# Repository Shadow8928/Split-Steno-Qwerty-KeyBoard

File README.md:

# Split-Steno-Qwerty-Keyboard

Modular and split keyboard designed to be affordable and easy to solder. 

Usage: create the 4 different pcbs and their respective cases solder all the components then flash the software (More detailes to be added later)
Taking inspiration from 2 keyboards a single keyboard used for stenography and another keyboard used for both stenography and qwerty typing i designed a keyboard with a layout of the 2 somewhat combined also split down the middle with a wire to connect them together. now the keyboard should be able to type in stenography for which it should have n-key rollover as well as all the keys to type regular qwerty style.   

The only requirements are a computer with the port to connect the keyboard and plover setup and configured on that same computer.

| Part    | Quantity | Price |
| ------- | -------- |-------|
| Type C recepticle 5 pack  |  1 | $2.44|
| RaspBerry Pi Pico | 2     |$5.20|
| Pogo connector 5 pack    | 1    |$1.23|
|Diodes 100pc|1|$1.88|
|Mechanical switches 50pc|1|$9.55|
|Total keyboard|1|$20.30|

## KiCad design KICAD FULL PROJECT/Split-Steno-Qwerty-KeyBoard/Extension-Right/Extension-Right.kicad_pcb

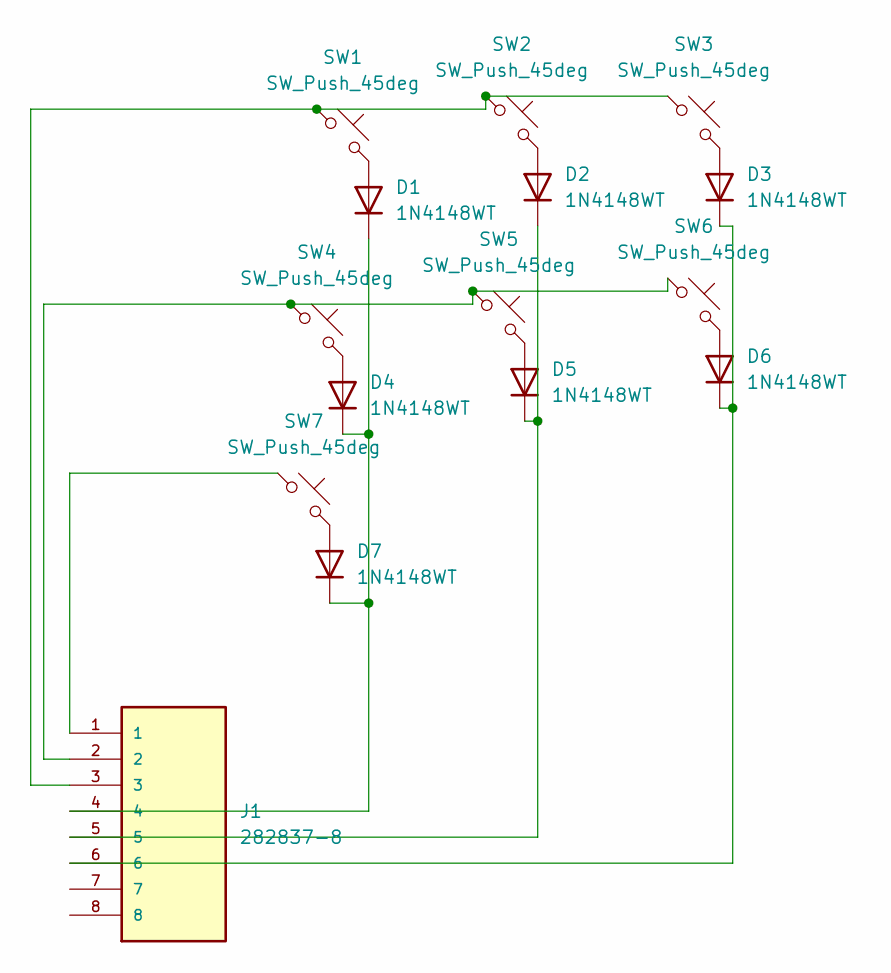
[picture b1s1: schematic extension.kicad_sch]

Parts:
D1, D2, D3, D4, D5, D6, D7: 1N4148WT; D_SOD-523
J1: 282837-8; TE_282837-8; PARTREV H
SW1, SW2, SW3, SW4, SW5, SW6, SW7: SW_Push_45deg; SW_Cherry_MX_1.00u_PCB

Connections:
unnamed: D1.2 (A), SW1.2
unnamed: D1.1 (K), D4.1 (K), D7.1 (K), J1.4
unnamed: D2.2 (A), SW2.2
unnamed: D2.1 (K), D5.1 (K), J1.5
unnamed: D3.2 (A), SW3.2
unnamed: D3.1 (K), D6.1 (K), J1.6
unnamed: D4.2 (A), SW4.2
unnamed: D5.2 (A), SW5.2
unnamed: D6.2 (A), SW6.2
unnamed: D7.2 (A), SW7.2
unnamed: J1.1, SW7.1
unnamed: J1.2, SW4.1, SW5.1, SW6.1
unnamed: J1.3, SW1.1, SW2.1, SW3.1

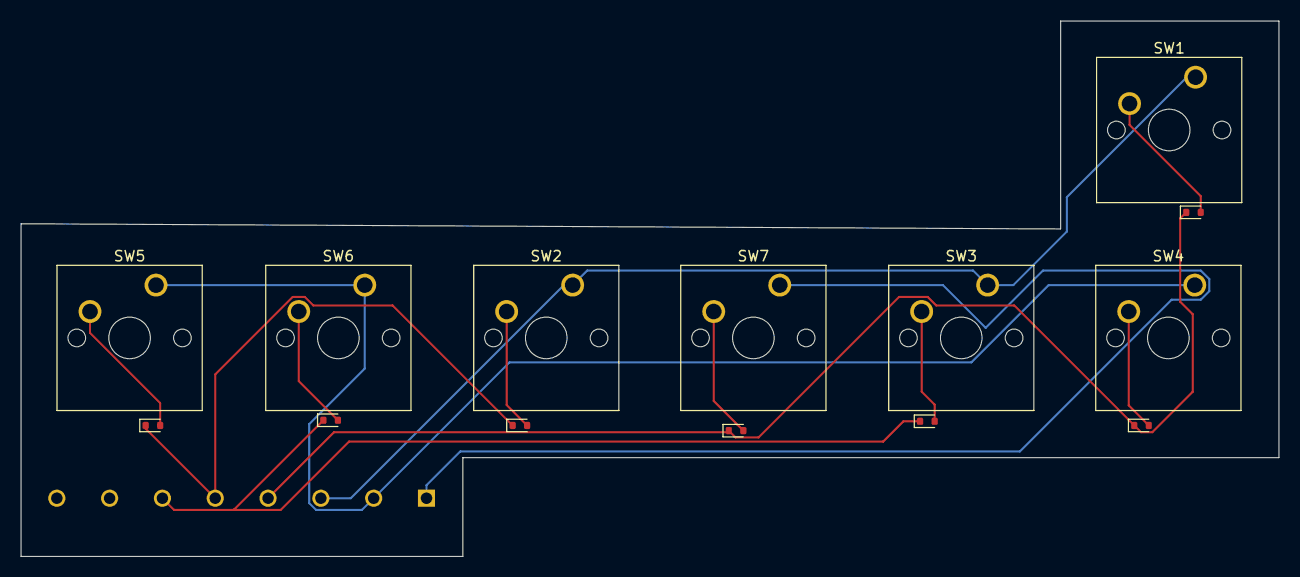
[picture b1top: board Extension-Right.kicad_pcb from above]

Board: 2 copper layers, 121.0 x 51.5 mm, 15 parts (1 on the bottom side), 13 nets.

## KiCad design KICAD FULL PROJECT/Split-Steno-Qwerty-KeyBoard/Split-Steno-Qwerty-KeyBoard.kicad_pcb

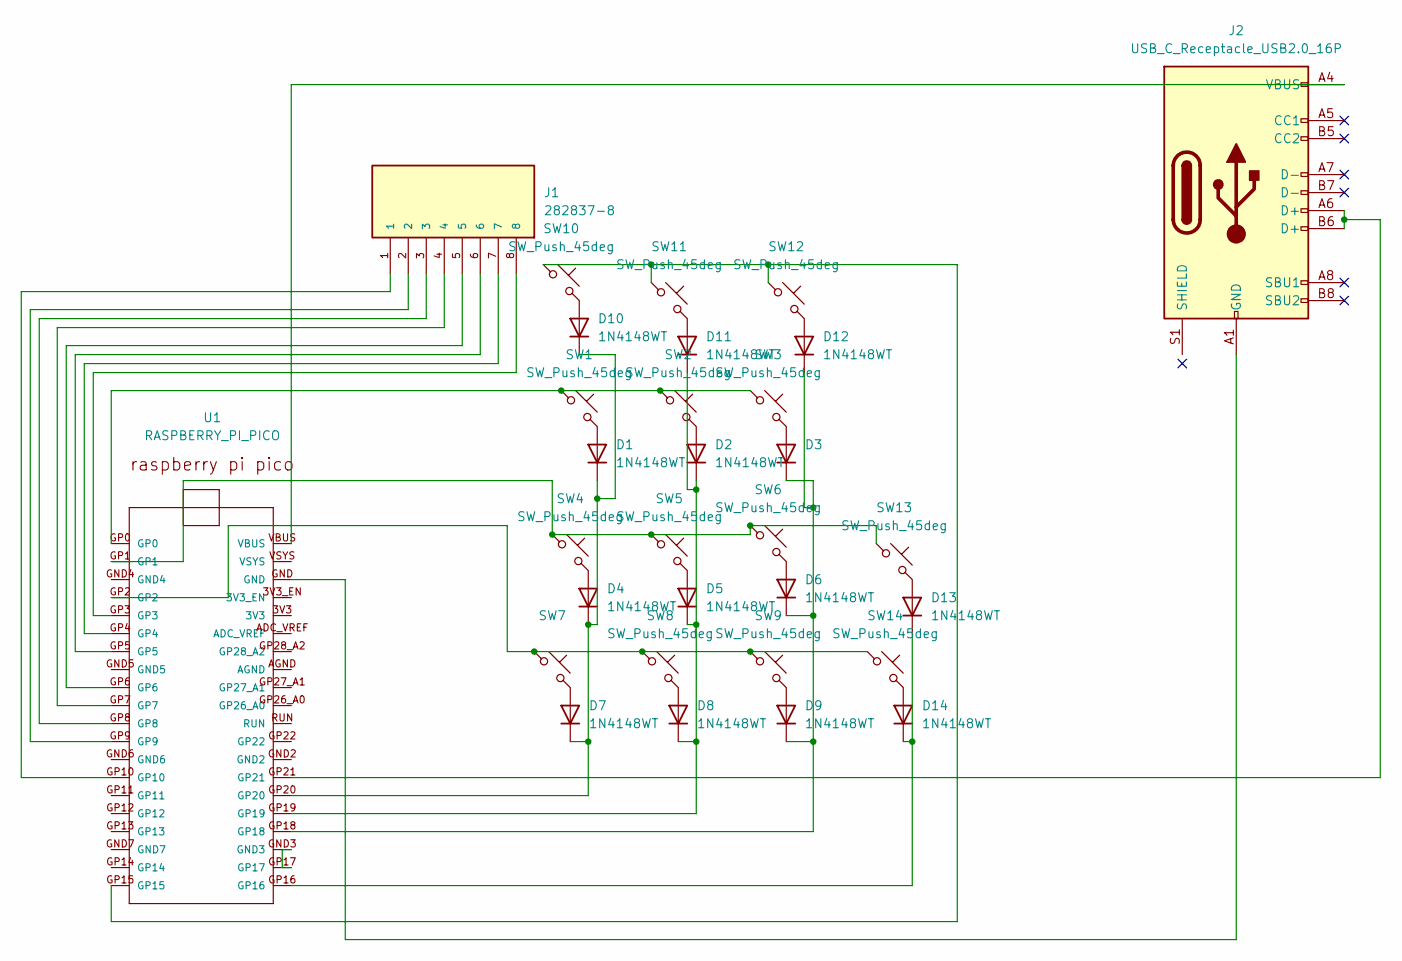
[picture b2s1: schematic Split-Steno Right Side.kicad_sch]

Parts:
D1, D2, D3, D4, D5, D6, D7, D8, D9, D10, D11, D12, D13, D14: 1N4148WT; D_SOD-523
J1: 282837-8; TE_282837-8; PARTREV H
J2: USB_C_Receptacle_USB2.0_16P; USB_C_Receptacle_XKB_U262-16XN-4BVC11
SW1, SW2, SW3, SW4, SW5, SW6, SW7, SW8, SW9, SW10, SW11, SW12, SW13, SW14: SW_Push_45deg; SW_MX_1u
U1: RASPBERRY_PI_PICO

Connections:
unnamed: D1.2 (A), SW1.2
unnamed: D1.1 (K), D4.1 (K), D7.1 (K), D10.1 (K), U1.GP20
unnamed: D2.2 (A), SW2.2
unnamed: D3.2 (A), SW3.2
unnamed: D4.2 (A), SW4.2
unnamed: D5.2 (A), SW5.2
unnamed: D6.2 (A), SW6.2
unnamed: D7.2 (A), SW7.2
unnamed: D8.2 (A), SW8.2
unnamed: D9.2 (A), SW9.2
unnamed: D10.2 (A), SW10.2
unnamed: D11.2 (A), SW11.2
unnamed: D2.1 (K), D5.1 (K), D8.1 (K), D11.1 (K), U1.GP19
unnamed: D12.2 (A), SW12.2
unnamed: D3.1 (K), D6.1 (K), D9.1 (K), D12.1 (K), U1.GP18
unnamed: D13.2 (A), SW13.2
unnamed: D13.1 (K), D14.1 (K), U1.GP16
unnamed: D14.2 (A), SW14.2
unnamed: J1.1, U1.GP10
unnamed: J1.2, U1.GP9
unnamed: J1.3, U1.GP8
unnamed: J1.4, U1.GP7
unnamed: J1.5, U1.GP6
unnamed: J1.6, U1.GP5
unnamed: J1.7, U1.GP4
unnamed: J1.8, U1.GP3
unnamed: J2.A6 (D+), J2.B6 (D+), U1.GP21
unnamed: J2.A1 (GND), J2.A12 (GND), J2.B1 (GND), J2.B12 (GND), U1.GND
unnamed: J2.A4 (VBUS), J2.A9 (VBUS), J2.B4 (VBUS), J2.B9 (VBUS), U1.VBUS
unnamed: SW1.1, SW2.1, SW3.1, U1.GP0
unnamed: SW10.1, SW11.1, SW12.1, U1.GP15
unnamed: SW4.1, SW5.1, SW6.1, SW13.1, U1.GP1
unnamed: SW7.1, SW8.1, SW9.1, SW14.1, U1.GP2
unnamed: U1.GND3, U1.GP17

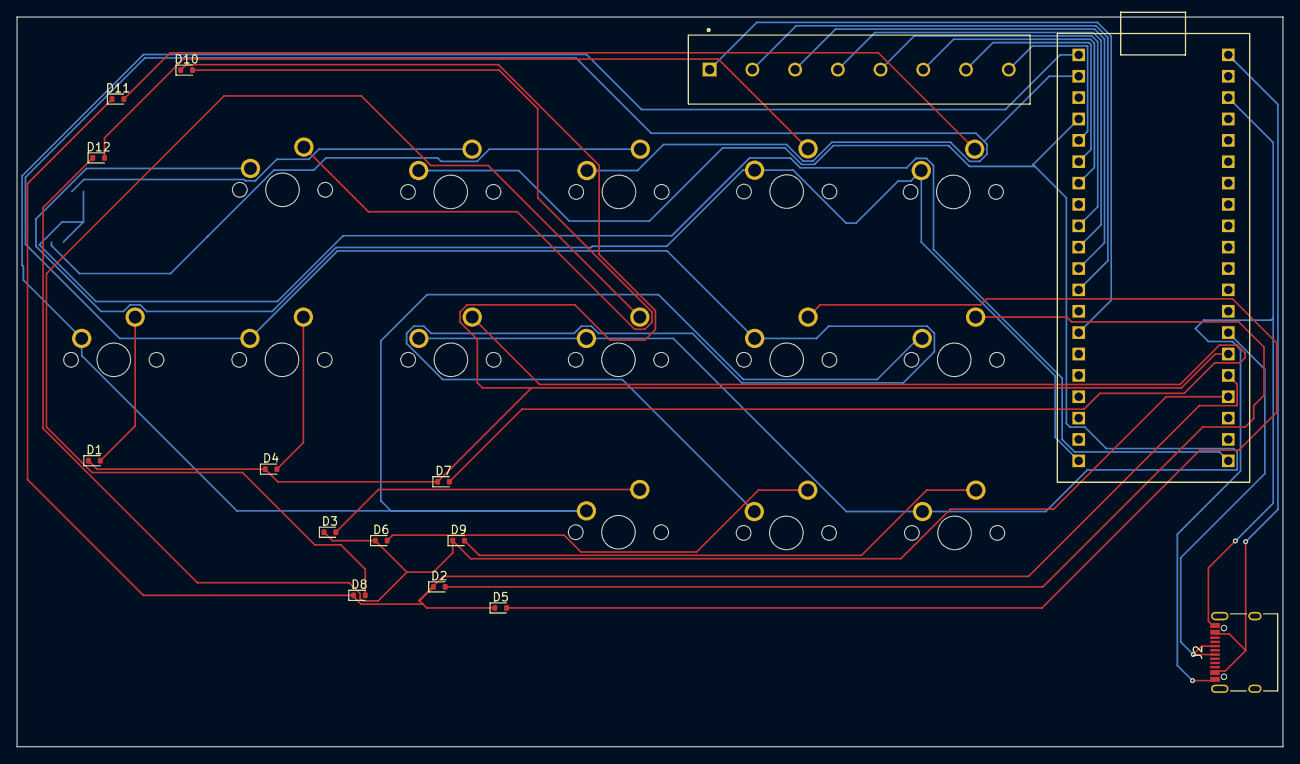
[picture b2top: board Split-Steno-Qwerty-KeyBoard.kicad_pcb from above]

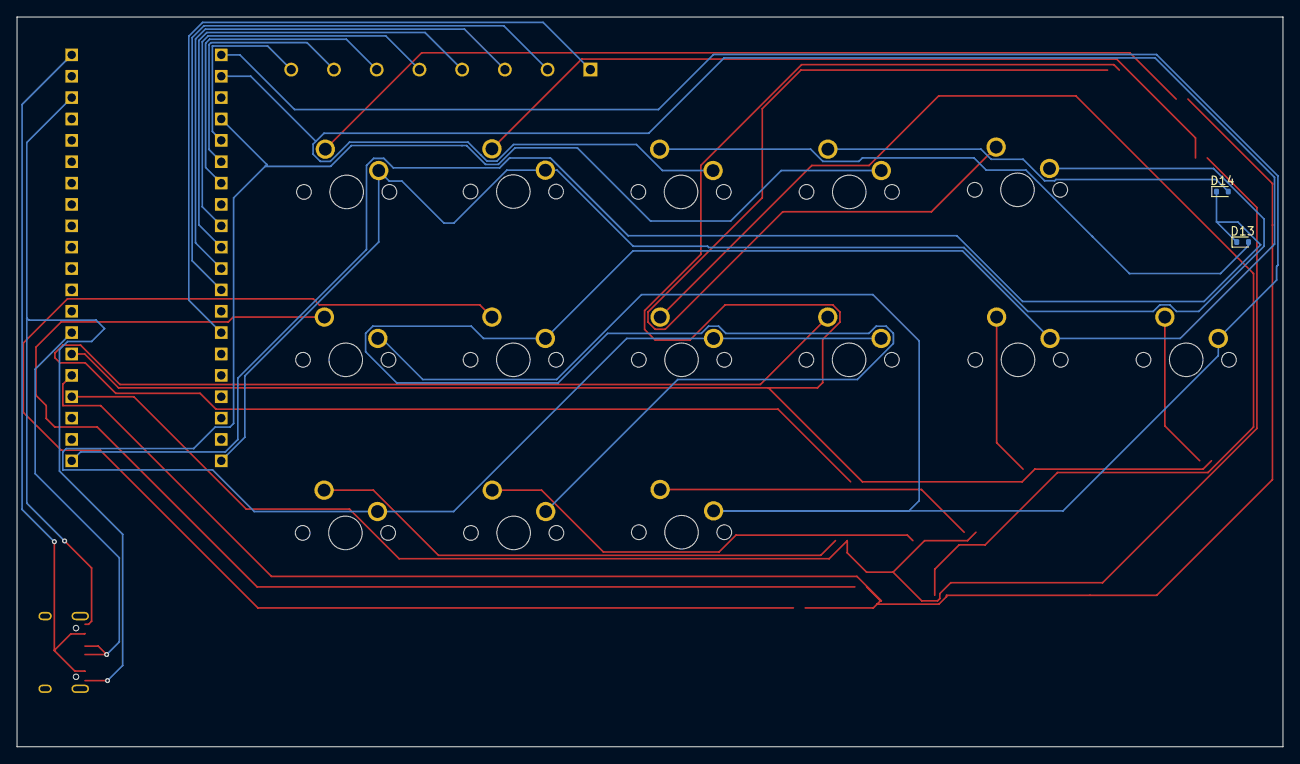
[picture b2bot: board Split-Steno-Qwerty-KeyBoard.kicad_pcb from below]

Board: 2 copper layers, 150.5 x 86.8 mm, 31 parts (2 on the bottom side), 34 nets.
